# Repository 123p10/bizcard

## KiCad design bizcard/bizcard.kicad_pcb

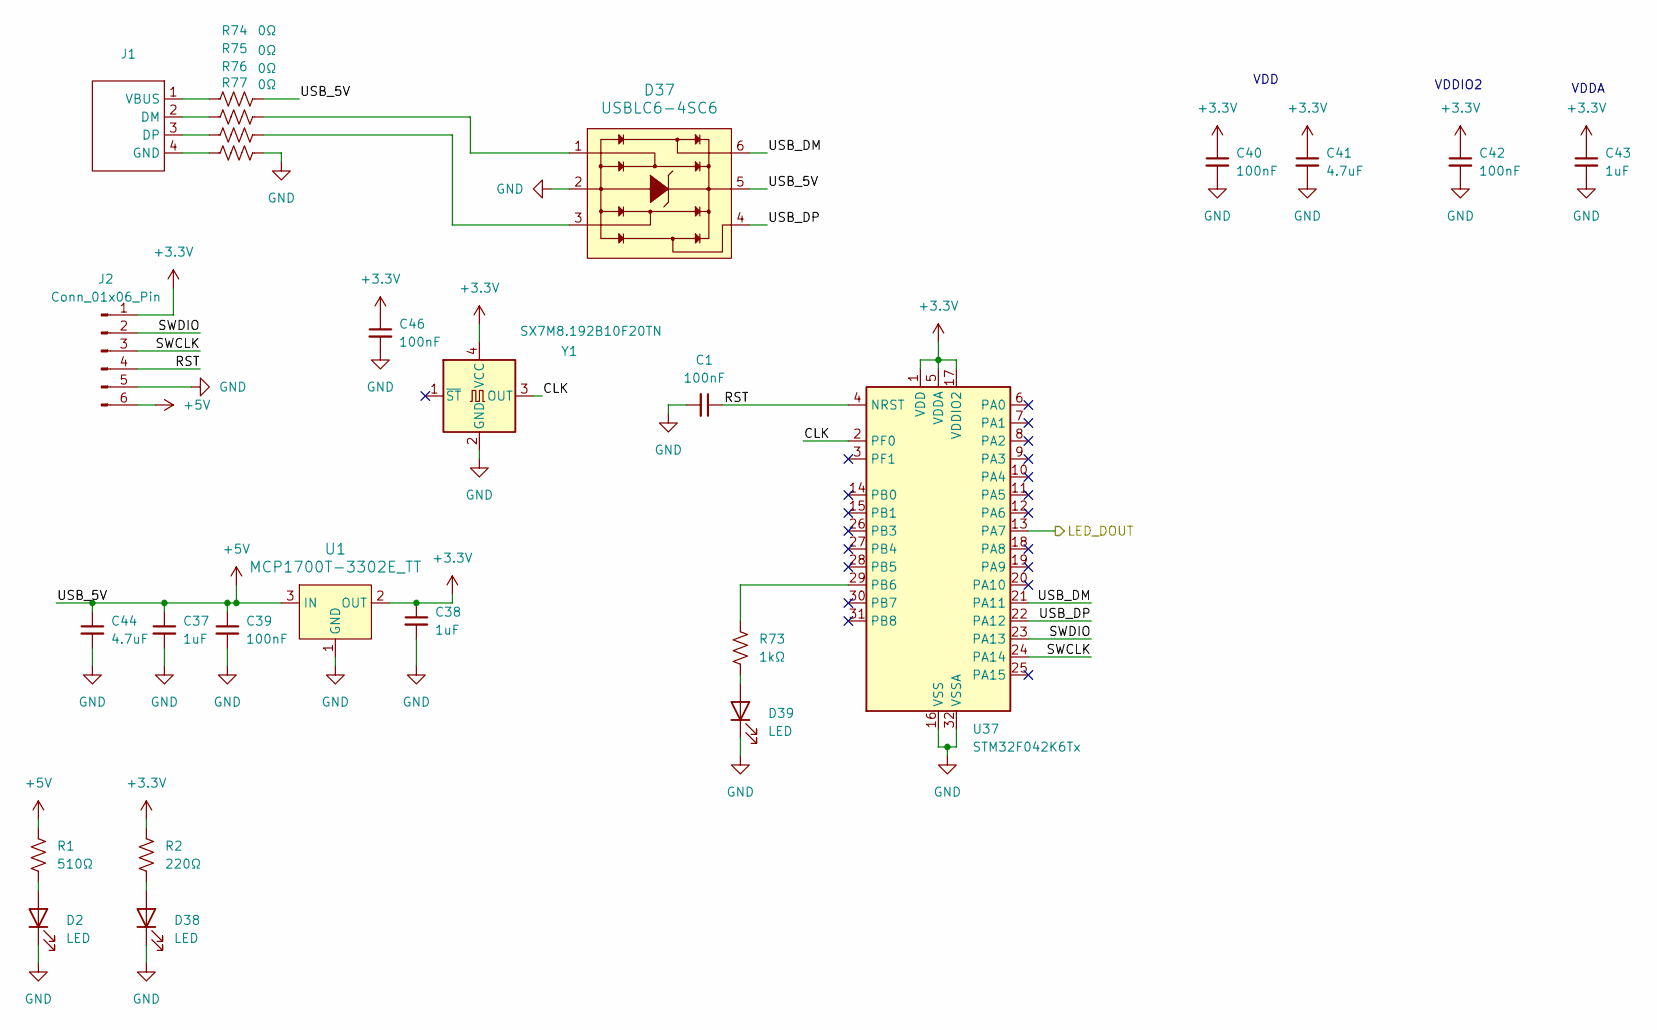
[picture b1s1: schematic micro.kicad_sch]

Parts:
C1, C39, C40, C42, C46: 100nF; C_0402_1005Metric
C37, C38, C43: 1uF; C_0402_1005Metric
C41: 4.7uF; C_0805_2012Metric
C44: 4.7uF; C_0603_1608Metric
D2, D38, D39: LED; LED_0603_1608Metric
D37: USBLC6-4SC6; SOT23-6L; MPN USBLC6-4SC6; Digi-Key_PN 497-4492-1-ND
J1: USB_PCBEDGE
J2: Conn_01x06_Pin; PinHeader_1x06_P2.54mm_Vertical
R1: 510Ω; R_0603_1608Metric
R2: 220Ω; R_0603_1608Metric
R73: 1kΩ; R_0603_1608Metric
R74, R75, R76, R77: 0Ω; R_0603_1608Metric
U1: MCP1700T-3302E_TT; SOT-23-3; MPN MCP1700T-3302E/TT; Digi-Key_PN MCP1700T3302ETTCT-ND
U37: STM32F042K6Tx; LQFP-32_7x7mm_P0.8mm
Y1: SX7M8.192B10F20TN; Oscillator_SMD_SeikoEpson_SG8002CA-4Pin_7.0x5.0mm

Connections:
+3.3V: C38.1, C40.1, C41.1, C42.1, C43.1, C46.1, J2.1, R2.1, U1.2 (OUT), U37.1 (VDD), U37.5 (VDDA), U37.17 (VDDIO2), Y1.4 (VCC)
+5V: C37.1, C39.1, C44.1, D37.5, J2.6, R1.1, R74.2, U1.3 (IN); also elsewhere on the board
/led/DIN: U37.13 (PA7); also elsewhere on the board
/micro/CLK: U37.2 (PF0), Y1.3 (OUT)
/micro/RST: C1.1, J2.4, U37.4 (NRST)
/micro/SWCLK: J2.3, U37.24 (PA14)
/micro/SWDIO: J2.2, U37.23 (PA13)
/micro/USB_DM: D37.6, U37.21 (PA11)
/micro/USB_DP: D37.4, U37.22 (PA12)
GND: C1.2, C37.2, C38.2, C39.2, C40.2, C41.2, C42.2, C43.2, C44.2, C46.2, D2.1 (K), D37.2, D38.1 (K), D39.1 (K), J2.5, R77.2, U1.1 (GND), U37.16 (VSS), U37.32 (VSSA), Y1.2 (GND); also elsewhere on the board
unnamed: D2.2 (A), R1.2
unnamed: D37.1, R75.2
unnamed: D37.3, R76.2
unnamed: D38.2 (A), R2.2
unnamed: D39.2 (A), R73.2
unnamed: J1.2 (DM), R75.1
unnamed: J1.3 (DP), R76.1
unnamed: J1.4 (GND), R77.1
unnamed: J1.1 (VBUS), R74.1
unnamed: R73.1, U37.29 (PB6)

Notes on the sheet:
VDDA
VDD
VDDIO2

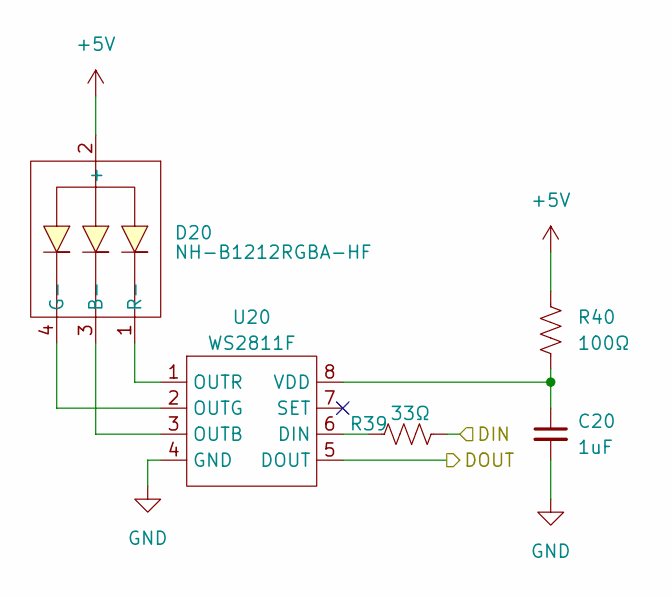
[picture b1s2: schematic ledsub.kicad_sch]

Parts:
C20: 1uF; C_0402_1005Metric
D20: NH-B1212RGBA-HF
R39: 33Ω; R_0402_1005Metric
R40: 100Ω; R_0402_1005Metric
U20: WS2811F

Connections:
+5V: D20.2 (+), R40.1; also elsewhere on the board
/led/ledsub_19/DIN: U20.5 (DOUT); also elsewhere on the board
/led/ledsub_20/DIN: R39.2; also elsewhere on the board
GND: C20.2, U20.4 (GND); also elsewhere on the board
unnamed: D20.3 (B-), U20.3 (OUTB)
unnamed: D20.4 (G-), U20.2 (OUTG)
unnamed: D20.1 (R-), U20.1 (OUTR)
unnamed: R39.1, U20.6 (DIN)
unnamed: C20.1, R40.2, U20.8 (VDD)

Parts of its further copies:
C2, C3, C4, C5, C6, C7, C8, C9, C10, C11, C12, C13, C14, C15, C16, C17, C18, C19, C21, C22, C23, C24, C25, C26, C27, C28, C29, C30, C31, C32, C33, C34, C35, C36, C45: 1uF; C_0402_1005Metric
D1, D3, D4, D5, D6, D7, D8, D9, D10, D11, D12, D13, D14, D15, D16, D17, D18, D19, D21, D22, D23, D24, D25, D26, D27, D28, D29, D30, D31, D32, D33, D34, D35, D36, D40: NH-B1212RGBA-HF
R3, R5, R7, R9, R11, R13, R15, R17, R19, R21, R23, R25, R27, R29, R31, R33, R35, R37, R41, R43, R45, R47, R49, R51, R53, R55, R57, R59, R61, R63, R65, R67, R69, R71, R78: 33Ω; R_0402_1005Metric
R4, R6, R8, R10, R12, R14, R16, R18, R20, R22, R24, R26, R28, R30, R32, R34, R36, R38, R42, R44, R46, R48, R50, R52, R54, R56, R58, R60, R62, R64, R66, R68, R70, R72, R79: 100Ω; R_0402_1005Metric
U2, U3, U4, U5, U6, U7, U8, U9, U10, U11, U12, U13, U14, U15, U16, U17, U18, U19, U21, U22, U23, U24, U25, U26, U27, U28, U29, U30, U31, U32, U33, U34, U35, U36, U38: WS2811F

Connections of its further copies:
+5V: D1.2 (+), D3.2 (+), D4.2 (+), D5.2 (+), D6.2 (+), D7.2 (+), D8.2 (+), D9.2 (+), D10.2 (+), D11.2 (+), D12.2 (+), D13.2 (+), D14.2 (+), D15.2 (+), D16.2 (+), D17.2 (+), D18.2 (+), D19.2 (+), D21.2 (+), D22.2 (+), D23.2 (+), D24.2 (+), D25.2 (+), D26.2 (+), D27.2 (+), D28.2 (+), D29.2 (+), D30.2 (+), D31.2 (+), D32.2 (+), D33.2 (+), D34.2 (+), D35.2 (+), D36.2 (+), D40.2 (+), R4.1, R6.1, R8.1, R10.1, R12.1, R14.1, R16.1, R18.1, R20.1, R22.1, R24.1, R26.1, R28.1, R30.1, R32.1, R34.1, R36.1, R38.1, R42.1, R44.1, R46.1, R48.1, R50.1, R52.1, R54.1, R56.1, R58.1, R60.1, R62.1, R64.1, R66.1, R68.1, R70.1, R72.1, R79.1; also elsewhere on the board
/led/DIN: R78.2; also elsewhere on the board
/led/ledsub_1/DOUT: R3.2, U38.5 (DOUT)
/led/ledsub_2/DOUT: R5.2, U2.5 (DOUT)
/led/ledsub_3/DOUT: R7.2, U3.5 (DOUT)
/led/ledsub_4/DOUT: R9.2, U4.5 (DOUT)
/led/ledsub_5/DOUT: R11.2, U5.5 (DOUT)
/led/ledsub_7/DIN: R13.2, U8.5 (DOUT)
/led/ledsub_8/DIN: R15.2, U9.5 (DOUT)
/led/ledsub_10/DIN: R19.2, U11.5 (DOUT)
/led/ledsub_10/DOUT: R17.2, U10.5 (DOUT)
/led/ledsub_11/DIN: R21.2, U12.5 (DOUT)
/led/ledsub_12/DIN: R23.2, U6.5 (DOUT)
/led/ledsub_13/DIN: R25.2, U7.5 (DOUT)
/led/ledsub_13/DOUT: R27.2, U13.5 (DOUT)
/led/ledsub_14/DOUT: R29.2, U14.5 (DOUT)
/led/ledsub_15/DOUT: R31.2, U15.5 (DOUT)
/led/ledsub_16/DOUT: R33.2, U16.5 (DOUT)
/led/ledsub_17/DOUT: R35.2, U17.5 (DOUT)
/led/ledsub_18/DOUT: R47.2, U18.5 (DOUT)
/led/ledsub_19/DIN: R37.2; also elsewhere on the board
/led/ledsub_19/DOUT: R49.2, U19.5 (DOUT)
/led/ledsub_20/DIN: U21.5 (DOUT); also elsewhere on the board
/led/ledsub_21/DIN: R41.2, U22.5 (DOUT)
/led/ledsub_22/DIN: R43.2, U23.5 (DOUT)
/led/ledsub_23/DIN: R45.2, U24.5 (DOUT)
/led/ledsub_25/DOUT: R51.2, U25.5 (DOUT)
/led/ledsub_26/DOUT: R53.2, U26.5 (DOUT)
/led/ledsub_27/DOUT: R55.2, U27.5 (DOUT)
/led/ledsub_28/DOUT: R57.2, U28.5 (DOUT)
/led/ledsub_29/DOUT: R59.2, U29.5 (DOUT)
/led/ledsub_30/DOUT: R71.2, U30.5 (DOUT)
/led/ledsub_31/DIN: R61.2, U32.5 (DOUT)
/led/ledsub_31/DOUT: U31.5 (DOUT)
/led/ledsub_32/DIN: R63.2, U33.5 (DOUT)
/led/ledsub_33/DIN: R65.2, U34.5 (DOUT)
/led/ledsub_34/DIN: R67.2, U35.5 (DOUT)
/led/ledsub_35/DIN: R69.2, U36.5 (DOUT)
GND: C2.2, C3.2, C4.2, C5.2, C6.2, C7.2, C8.2, C9.2, C10.2, C11.2, C12.2, C13.2, C14.2, C15.2, C16.2, C17.2, C18.2, C19.2, C21.2, C22.2, C23.2, C24.2, C25.2, C26.2, C27.2, C28.2, C29.2, C30.2, C31.2, C32.2, C33.2, C34.2, C35.2, C36.2, C45.2, U2.4 (GND), U3.4 (GND), U4.4 (GND), U5.4 (GND), U6.4 (GND), U7.4 (GND), U8.4 (GND), U9.4 (GND), U10.4 (GND), U11.4 (GND), U12.4 (GND), U13.4 (GND), U14.4 (GND), U15.4 (GND), U16.4 (GND), U17.4 (GND), U18.4 (GND), U19.4 (GND), U21.4 (GND), U22.4 (GND), U23.4 (GND), U24.4 (GND), U25.4 (GND), U26.4 (GND), U27.4 (GND), U28.4 (GND), U29.4 (GND), U30.4 (GND), U31.4 (GND), U32.4 (GND), U33.4 (GND), U34.4 (GND), U35.4 (GND), U36.4 (GND), U38.4 (GND); also elsewhere on the board
unnamed: D1.3 (B-), U2.3 (OUTB)
unnamed: D1.4 (G-), U2.2 (OUTG)
unnamed: D1.1 (R-), U2.1 (OUTR)
unnamed: D3.3 (B-), U3.3 (OUTB)
unnamed: D3.4 (G-), U3.2 (OUTG)
unnamed: D3.1 (R-), U3.1 (OUTR)
unnamed: D4.3 (B-), U4.3 (OUTB)
unnamed: D4.4 (G-), U4.2 (OUTG)
unnamed: D4.1 (R-), U4.1 (OUTR)
unnamed: D5.3 (B-), U5.3 (OUTB)
unnamed: D5.4 (G-), U5.2 (OUTG)
unnamed: D5.1 (R-), U5.1 (OUTR)
unnamed: D6.3 (B-), U6.3 (OUTB)
unnamed: D6.4 (G-), U6.2 (OUTG)
unnamed: D6.1 (R-), U6.1 (OUTR)
unnamed: D7.3 (B-), U7.3 (OUTB)
unnamed: D7.4 (G-), U7.2 (OUTG)
unnamed: D7.1 (R-), U7.1 (OUTR)
unnamed: D8.3 (B-), U8.3 (OUTB)
unnamed: D8.4 (G-), U8.2 (OUTG)
unnamed: D8.1 (R-), U8.1 (OUTR)
unnamed: D9.3 (B-), U9.3 (OUTB)
unnamed: D9.4 (G-), U9.2 (OUTG)
unnamed: D9.1 (R-), U9.1 (OUTR)
unnamed: D10.3 (B-), U10.3 (OUTB)
unnamed: D10.4 (G-), U10.2 (OUTG)
unnamed: D10.1 (R-), U10.1 (OUTR)
unnamed: D11.3 (B-), U11.3 (OUTB)
unnamed: D11.4 (G-), U11.2 (OUTG)
unnamed: D11.1 (R-), U11.1 (OUTR)
unnamed: D12.3 (B-), U12.3 (OUTB)
unnamed: D12.4 (G-), U12.2 (OUTG)
unnamed: D12.1 (R-), U12.1 (OUTR)
unnamed: D13.3 (B-), U13.3 (OUTB)
unnamed: D13.4 (G-), U13.2 (OUTG)
unnamed: D13.1 (R-), U13.1 (OUTR)
unnamed: D14.3 (B-), U14.3 (OUTB)
unnamed: D14.4 (G-), U14.2 (OUTG)
unnamed: D14.1 (R-), U14.1 (OUTR)
unnamed: D15.3 (B-), U15.3 (OUTB)
unnamed: D15.4 (G-), U15.2 (OUTG)
unnamed: D15.1 (R-), U15.1 (OUTR)
unnamed: D16.3 (B-), U16.3 (OUTB)
unnamed: D16.4 (G-), U16.2 (OUTG)
unnamed: D16.1 (R-), U16.1 (OUTR)
unnamed: D17.3 (B-), U17.3 (OUTB)
unnamed: D17.4 (G-), U17.2 (OUTG)
unnamed: D17.1 (R-), U17.1 (OUTR)
unnamed: D18.3 (B-), U18.3 (OUTB)
unnamed: D18.4 (G-), U18.2 (OUTG)
unnamed: D18.1 (R-), U18.1 (OUTR)
unnamed: D19.3 (B-), U19.3 (OUTB)
unnamed: D19.4 (G-), U19.2 (OUTG)
unnamed: D19.1 (R-), U19.1 (OUTR)
unnamed: D21.3 (B-), U21.3 (OUTB)
unnamed: D21.4 (G-), U21.2 (OUTG)
unnamed: D21.1 (R-), U21.1 (OUTR)
unnamed: D22.3 (B-), U22.3 (OUTB)
unnamed: D22.4 (G-), U22.2 (OUTG)
unnamed: D22.1 (R-), U22.1 (OUTR)
unnamed: D23.3 (B-), U23.3 (OUTB)
unnamed: D23.4 (G-), U23.2 (OUTG)
unnamed: D23.1 (R-), U23.1 (OUTR)
unnamed: D24.3 (B-), U24.3 (OUTB)
unnamed: D24.4 (G-), U24.2 (OUTG)
unnamed: D24.1 (R-), U24.1 (OUTR)
unnamed: D25.3 (B-), U25.3 (OUTB)
unnamed: D25.4 (G-), U25.2 (OUTG)
unnamed: D25.1 (R-), U25.1 (OUTR)
unnamed: D26.3 (B-), U26.3 (OUTB)
unnamed: D26.4 (G-), U26.2 (OUTG)
unnamed: D26.1 (R-), U26.1 (OUTR)
unnamed: D27.3 (B-), U27.3 (OUTB)
unnamed: D27.4 (G-), U27.2 (OUTG)
unnamed: D27.1 (R-), U27.1 (OUTR)
unnamed: D28.3 (B-), U28.3 (OUTB)
unnamed: D28.4 (G-), U28.2 (OUTG)
unnamed: D28.1 (R-), U28.1 (OUTR)
unnamed: D29.3 (B-), U29.3 (OUTB)
unnamed: D29.4 (G-), U29.2 (OUTG)
unnamed: D29.1 (R-), U29.1 (OUTR)
unnamed: D30.3 (B-), U30.3 (OUTB)
unnamed: D30.4 (G-), U30.2 (OUTG)
unnamed: D30.1 (R-), U30.1 (OUTR)
unnamed: D31.3 (B-), U31.3 (OUTB)
unnamed: D31.4 (G-), U31.2 (OUTG)
unnamed: D31.1 (R-), U31.1 (OUTR)
unnamed: D32.3 (B-), U32.3 (OUTB)
unnamed: D32.4 (G-), U32.2 (OUTG)
unnamed: D32.1 (R-), U32.1 (OUTR)
unnamed: D33.3 (B-), U33.3 (OUTB)
unnamed: D33.4 (G-), U33.2 (OUTG)
unnamed: D33.1 (R-), U33.1 (OUTR)
unnamed: D34.3 (B-), U34.3 (OUTB)
unnamed: D34.4 (G-), U34.2 (OUTG)
unnamed: D34.1 (R-), U34.1 (OUTR)
unnamed: D35.3 (B-), U35.3 (OUTB)
unnamed: D35.4 (G-), U35.2 (OUTG)
unnamed: D35.1 (R-), U35.1 (OUTR)
unnamed: D36.3 (B-), U36.3 (OUTB)
unnamed: D36.4 (G-), U36.2 (OUTG)
unnamed: D36.1 (R-), U36.1 (OUTR)
unnamed: D40.3 (B-), U38.3 (OUTB)
unnamed: D40.4 (G-), U38.2 (OUTG)
unnamed: D40.1 (R-), U38.1 (OUTR)
unnamed: R3.1, U2.6 (DIN)
unnamed: C2.1, R4.2, U2.8 (VDD)
unnamed: R5.1, U3.6 (DIN)
unnamed: C3.1, R6.2, U3.8 (VDD)
unnamed: R7.1, U4.6 (DIN)
unnamed: C4.1, R8.2, U4.8 (VDD)
unnamed: R9.1, U5.6 (DIN)
unnamed: C5.1, R10.2, U5.8 (VDD)
unnamed: R11.1, U6.6 (DIN)
unnamed: C6.1, R12.2, U6.8 (VDD)
unnamed: R13.1, U7.6 (DIN)
unnamed: C7.1, R14.2, U7.8 (VDD)
unnamed: R15.1, U8.6 (DIN)
unnamed: C8.1, R16.2, U8.8 (VDD)
unnamed: R17.1, U9.6 (DIN)
unnamed: C9.1, R18.2, U9.8 (VDD)
unnamed: R19.1, U10.6 (DIN)
unnamed: C10.1, R20.2, U10.8 (VDD)
unnamed: R21.1, U11.6 (DIN)
unnamed: C11.1, R22.2, U11.8 (VDD)
unnamed: R23.1, U12.6 (DIN)
unnamed: C12.1, R24.2, U12.8 (VDD)
unnamed: R25.1, U13.6 (DIN)
unnamed: C13.1, R26.2, U13.8 (VDD)
unnamed: R27.1, U14.6 (DIN)
unnamed: C14.1, R28.2, U14.8 (VDD)
unnamed: R29.1, U15.6 (DIN)
unnamed: C15.1, R30.2, U15.8 (VDD)
unnamed: R31.1, U16.6 (DIN)
unnamed: C16.1, R32.2, U16.8 (VDD)
unnamed: R33.1, U17.6 (DIN)
unnamed: C17.1, R34.2, U17.8 (VDD)
unnamed: R35.1, U18.6 (DIN)
unnamed: C18.1, R36.2, U18.8 (VDD)
unnamed: R37.1, U19.6 (DIN)
unnamed: C19.1, R38.2, U19.8 (VDD)
unnamed: R41.1, U21.6 (DIN)
unnamed: C21.1, R42.2, U21.8 (VDD)
unnamed: R43.1, U22.6 (DIN)
unnamed: C22.1, R44.2, U22.8 (VDD)
unnamed: R45.1, U23.6 (DIN)
unnamed: C23.1, R46.2, U23.8 (VDD)
unnamed: R47.1, U24.6 (DIN)
unnamed: C24.1, R48.2, U24.8 (VDD)
unnamed: R49.1, U25.6 (DIN)
unnamed: C25.1, R50.2, U25.8 (VDD)
unnamed: R51.1, U26.6 (DIN)
unnamed: C26.1, R52.2, U26.8 (VDD)
unnamed: R53.1, U27.6 (DIN)
unnamed: C27.1, R54.2, U27.8 (VDD)
unnamed: R55.1, U28.6 (DIN)
unnamed: C28.1, R56.2, U28.8 (VDD)
unnamed: R57.1, U29.6 (DIN)
unnamed: C29.1, R58.2, U29.8 (VDD)
unnamed: R59.1, U30.6 (DIN)
unnamed: C30.1, R60.2, U30.8 (VDD)
unnamed: R61.1, U31.6 (DIN)
unnamed: C31.1, R62.2, U31.8 (VDD)
unnamed: R63.1, U32.6 (DIN)
unnamed: C32.1, R64.2, U32.8 (VDD)
unnamed: R65.1, U33.6 (DIN)
unnamed: C33.1, R66.2, U33.8 (VDD)
unnamed: R67.1, U34.6 (DIN)
unnamed: C34.1, R68.2, U34.8 (VDD)
unnamed: R69.1, U35.6 (DIN)
unnamed: C35.1, R70.2, U35.8 (VDD)
unnamed: R71.1, U36.6 (DIN)
unnamed: C36.1, R72.2, U36.8 (VDD)
unnamed: R78.1, U38.6 (DIN)
unnamed: C45.1, R79.2, U38.8 (VDD)

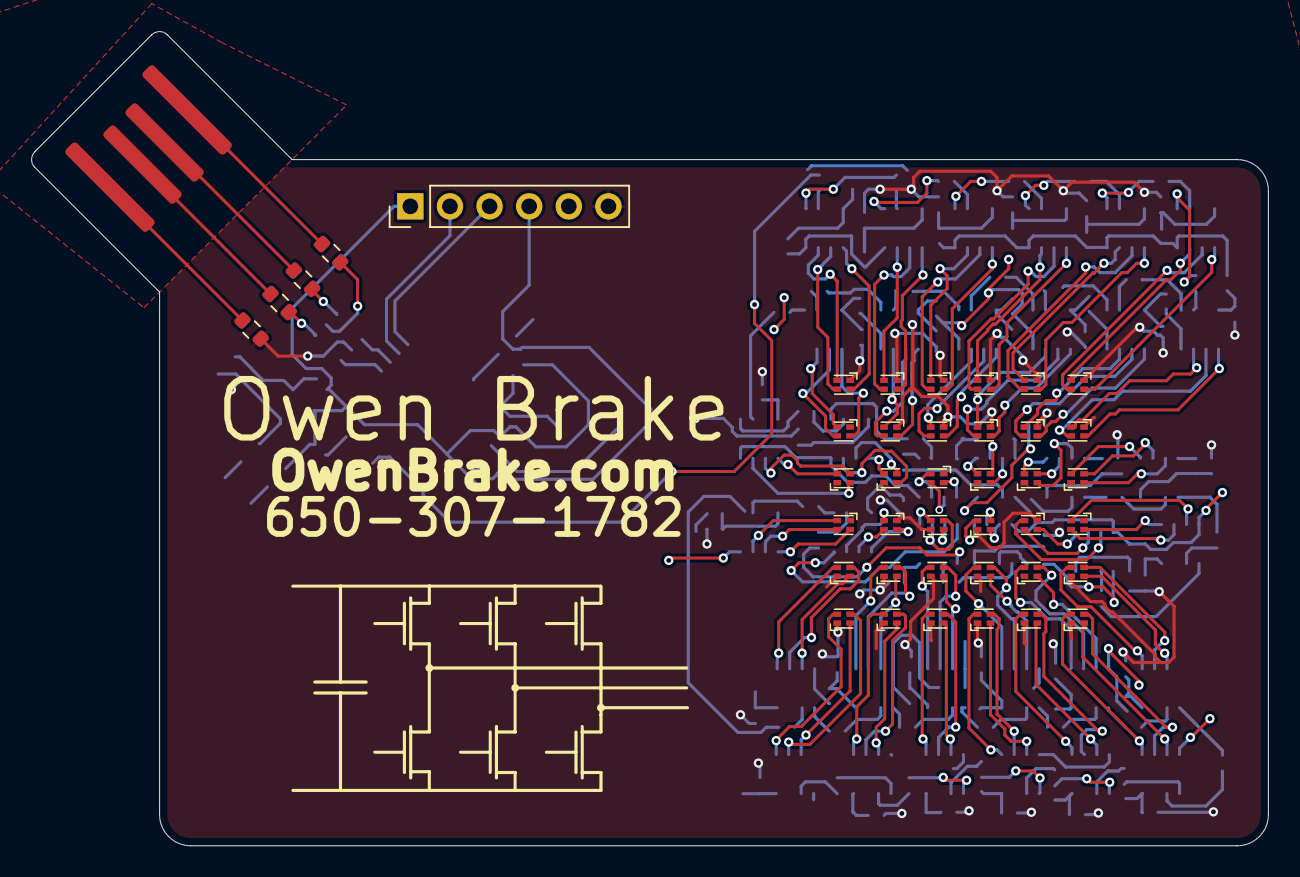
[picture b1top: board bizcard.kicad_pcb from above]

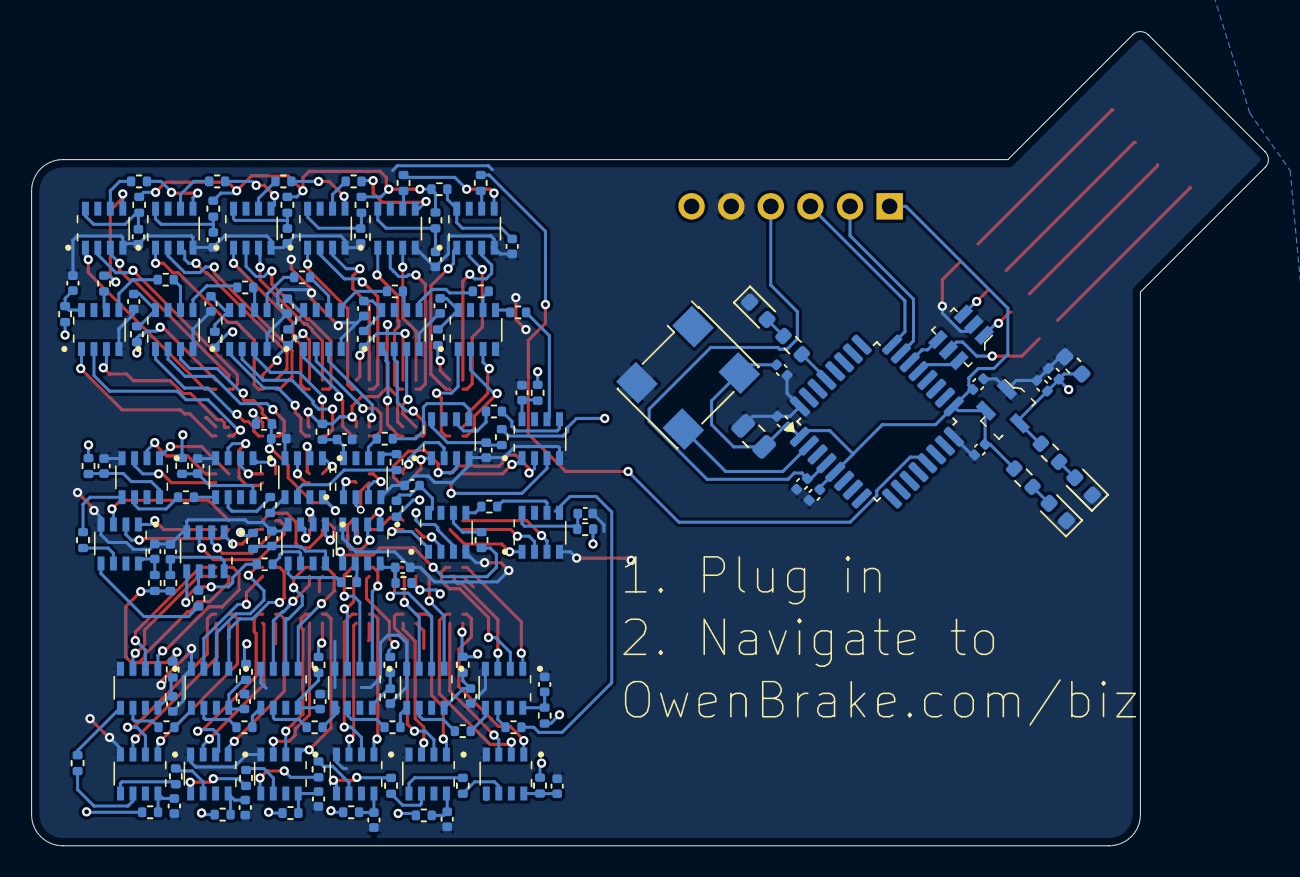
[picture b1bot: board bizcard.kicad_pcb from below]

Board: 2 copper layers, 79.3 x 52.2 mm, 206 parts (164 on the bottom side), 235 nets.

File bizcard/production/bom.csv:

Designator,Footprint,Quantity,Value,LCSC Part #
"C1, C39, C40, C42, C46",0402,5,100nF,
"C10, C11, C12, C13, C14, C15, C16, C17, C18, C19, C2, C20, C21, C22, C23, C24, C25, C26, C27, C28, C29, C3, C30, C31, C32, C33, C34, C35, C36, C37, C38, C4, C43, C45, C5, C6, C7, C8, C9",0402,39,1uF,
C41,0805,1,4.7uF,
C44,0603,1,4.7uF,
"D1, D10, D11, D12, D13, D14, D15, D16, D17, D18, D19, D20, D21, D22, D23, D24, D25, D26, D27, D28, D29, D3, D30, D31, D32, D33, D34, D35, D36, D4, D40, D5, D6, D7, D8, D9",NH-B1212RGBA-HF,36,NH-B1212RGBA-HF,
"D2, D38, D39",0603,3,LED,
D37,SOT23-6L,1,USBLC6-4SC6,USBLC6-4SC6
J1,USB_PCBEDGE,1,~,
J2,PinHeader_1x06_P2.54mm_Vertical,1,Conn_01x06_Pin,
R1,0603,1,510Ω,
"R10, R12, R14, R16, R18, R20, R22, R24, R26, R28, R30, R32, R34, R36, R38, R4, R40, R42, R44, R46, R48, R50, R52, R54, R56, R58, R6, R60, R62, R64, R66, R68, R70, R72, R79, R8",0402,36,100Ω,
"R11, R13, R15, R17, R19, R21, R23, R25, R27, R29, R3, R31, R33, R35, R37, R39, R41, R43, R45, R47, R49, R5, R51, R53, R55, R57, R59, R61, R63, R65, R67, R69, R7, R71, R78, R9",0402,36,33Ω,
R2,0603,1,220Ω,
R73,0603,1,1kΩ,
"R74, R75, R76, R77",0603,4,0Ω,
U1,SOT-23-3,1,MCP1700T-3302E_TT,MCP1700T-3302E/TT
"U10, U11, U12, U13, U14, U15, U16, U17, U18, U19, U2, U20, U21, U22, U23, U24, U25, U26, U27, U28, U29, U3, U30, U31, U32, U33, U34, U35, U36, U38, U4, U5, U6, U7, U8, U9",WS2811F,36,WS2811F,
U37,LQFP-32_7x7mm_P0.8mm,1,STM32F042K6Tx,
Y1,Oscillator_SMD_SeikoEpson_SG8002CA-4Pin_7.0x5.0mm,1,SX7M8.192B10F20TN,

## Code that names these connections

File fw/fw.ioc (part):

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Mcu.Name=STM32F042K(4-6)Tx
Mcu.Package=LQFP32
Mcu.UserName=STM32F042K4Tx
PA11.Mode=Device
PA11.Signal=USB_DM
PA12.Mode=Device
PA12.Signal=USB_DP
PA13.Mode=Serial_Wire
PA13.Signal=SYS_SWDIO
PA14.Mode=Serial_Wire
PA14.Signal=SYS_SWCLK
PA5.Mode=Simplex_Bidirectional_Master
PA5.Signal=SPI1_SCK
PA7.Mode=Simplex_Bidirectional_Master
PA7.Signal=SPI1_MOSI
PB6.Signal=GPIO_Output
PF0-OSC_IN.Mode=HSE-External-Oscillator
PF0-OSC_IN.Signal=RCC_OSC_IN
PF1-OSC_OUT.Mode=HSE-External-Oscillator
PF1-OSC_OUT.Signal=RCC_OSC_OUT
RCC.SYSCLKFreq_VALUE=48000000
RCC.SYSCLKSource=RCC_SYSCLKSOURCE_HSI48
board=custom

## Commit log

2024-10-30 Push bizcard
2024-10-30 Push
2024-10-30 Business card
2024-11-01 Sync
2024-11-01 zoop
2024-11-01 Margin rules
2024-11-01 Shift
2024-11-01 new DRC
2024-11-01 zirp
2024-11-01 more
2024-11-01 Zipp
2024-11-01 Send
2024-11-01 Curved Edges
2024-11-01 Here
2024-11-01 Before txt change
2024-11-01 Production files
2024-11-01 Grep
2024-11-15 Drip
2024-11-15 LEDs driving
2024-11-16 Me Espresso
2024-11-16 Grinding
